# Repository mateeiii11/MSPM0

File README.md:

# MSPM0
MSMP0 designed in KiCad

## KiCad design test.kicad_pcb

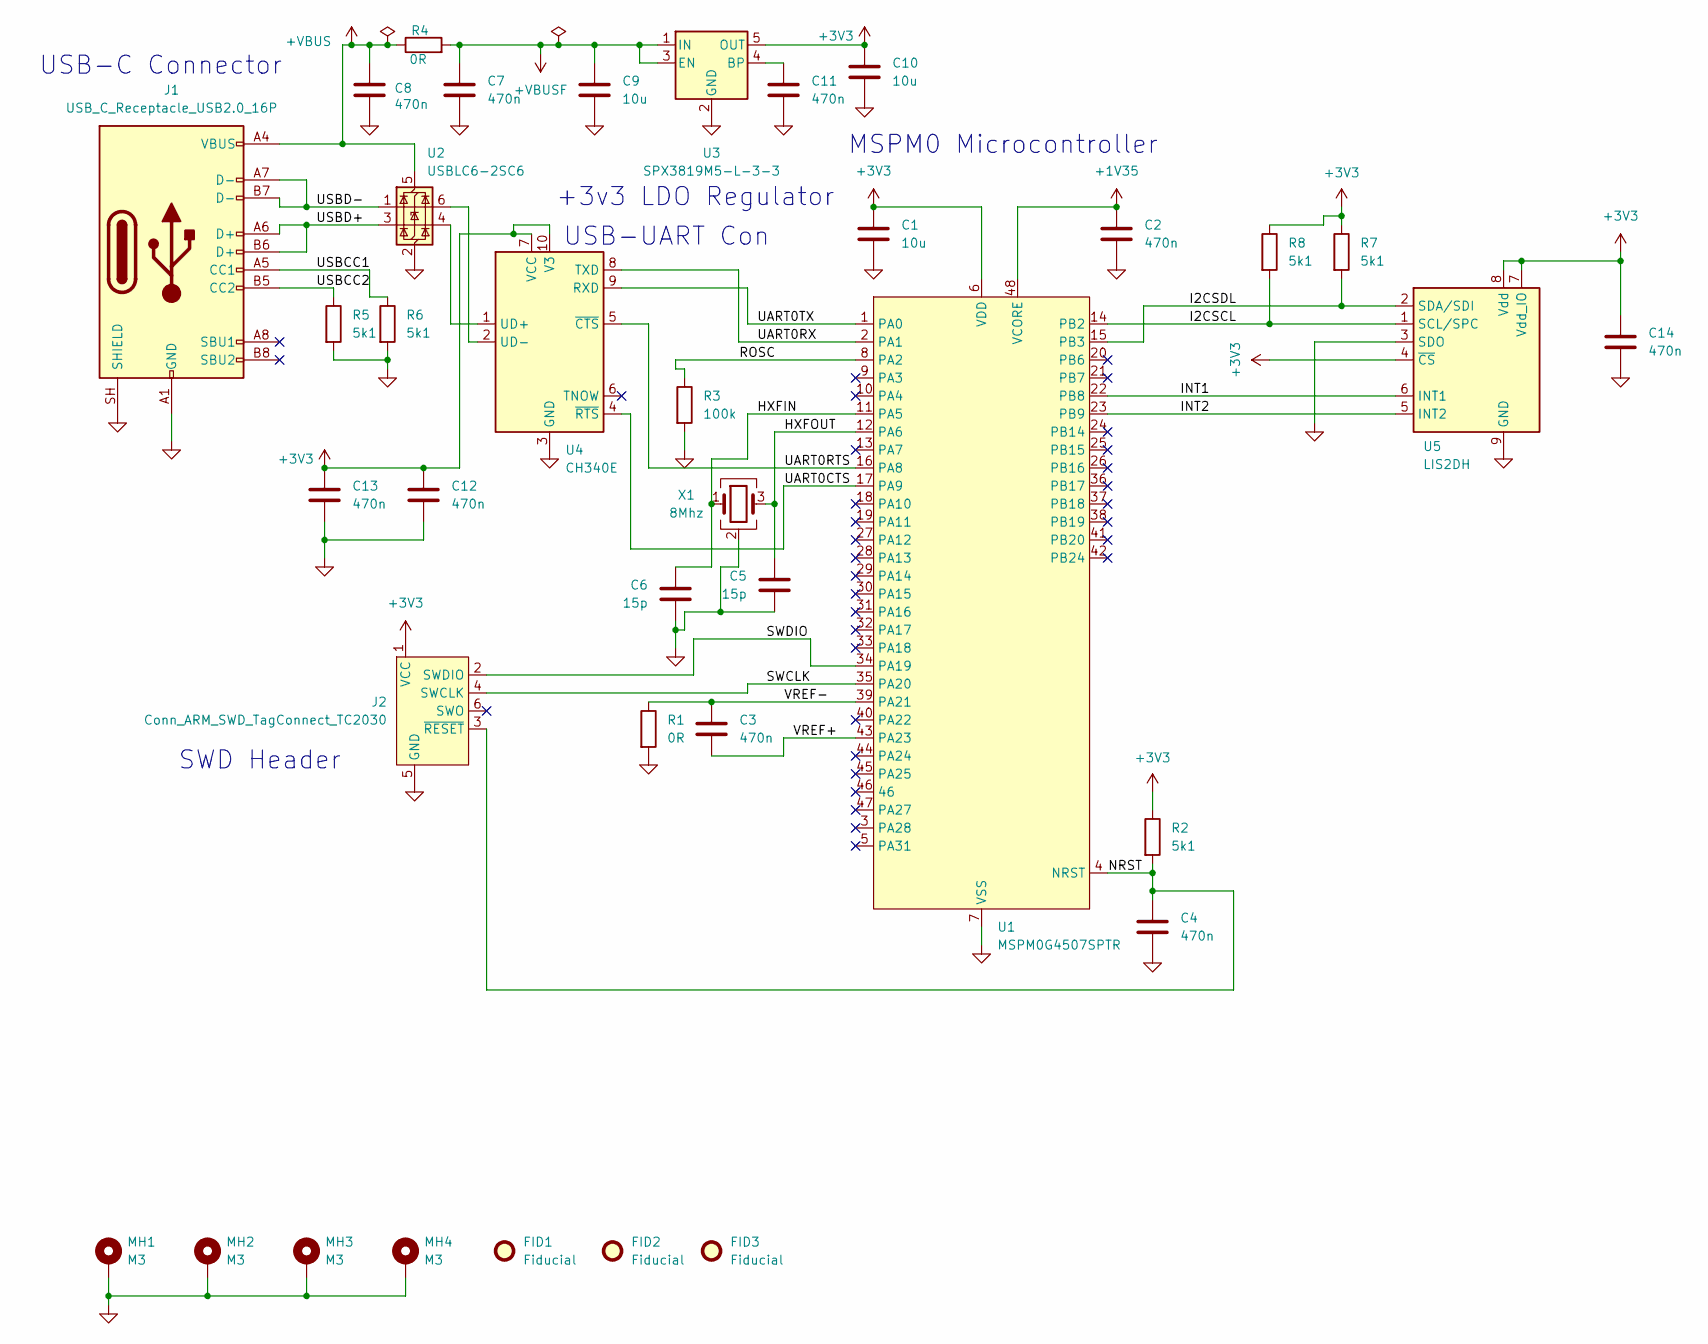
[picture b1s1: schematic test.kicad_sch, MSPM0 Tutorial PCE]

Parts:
C1, C9, C10: 10u; C_0805_2012Metric
C2, C3, C4, C7, C8, C11, C12, C13, C14: 470n; C_0805_2012Metric
C5, C6: 15p; C_0805_2012Metric
FID1, FID2, FID3: Fiducial; Fiducial_1mm_Mask2mm
J1: USB_C_Receptacle_USB2.0_16P; USB_C_Receptacle_GCT_USB4105-xx-A_16P_TopMnt_Horizontal
J2: Conn_ARM_SWD_TagConnect_TC2030; Tag-Connect_TC2030-IDC-FP_2x03_P1.27mm_Vertical
MH1, MH2, MH3, MH4: M3; MountingHole_3mm_Pad_Via
R1, R4: 0R; R_0603_1608Metric
R2, R5, R6, R7, R8: 5k1; R_0603_1608Metric
R3: 100k; R_0603_1608Metric
U1: MSPM0G4507SPTR; LQFP-48_7x7mm_P0.5mm; Manufacturer Part Number MSPM0G4507SPTR; LCSC C22362630
U2: USBLC6-2SC6; SOT-23-6
U3: SPX3819M5-L-3-3; SOT-23-5
U4: CH340E; MSOP-10_3x3mm_P0.5mm
U5: LIS2DH; LGA-14_2x2mm_P0.35mm_LayoutBorder3x4y
X1: 8Mhz; Crystal_SMD_3225-4Pin_3.2x2.5mm

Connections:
+1V35: C2.1, U1.48 (VCORE)
+3V3: C1.1, C10.1, C12.1, C13.1, C14.1, J2.1 (VCC), R2.1, R7.1, R8.1, U1.6 (VDD), U3.5 (OUT), U4.7 (VCC), U4.10 (V3), U5.4 (~CS), U5.7 (Vdd_IO), U5.8 (Vdd)
+VBUS: C8.1, J1.A4 (VBUS), J1.A9 (VBUS), J1.B4 (VBUS), J1.B9 (VBUS), R4.1, U2.5 (VBUS)
+VBUSF: C7.1, C9.1, R4.2, U3.1 (IN), U3.3 (EN)
/HXFIN: C6.1, U1.11 (PA5), X1.1
/HXFOUT: C5.1, U1.12 (PA6), X1.3
/I2CSCL: R8.2, U1.14 (PB2), U5.1 (SCL/SPC)
/I2CSDL: R7.2, U1.15 (PB3), U5.2 (SDA/SDI)
/INT1: U1.22 (PB8), U5.6 (INT1)
/INT2: U1.23 (PB9), U5.5 (INT2)
/NRST: C4.1, J2.3 (~RESET), R2.2, U1.4 (NRST)
/ROSC: R3.1, U1.8 (PA2)
/SWCLK: J2.4 (SWCLK), U1.35 (PA20)
/SWDIO: J2.2 (SWDIO), U1.34 (PA19)
/UART0CTS: U1.17 (PA9), U4.4 (~RTS)
/UART0RTS: U1.16 (PA8), U4.5 (~CTS)
/UART0RX: U1.2 (PA1), U4.8 (TXD)
/UART0TX: U1.1 (PA0), U4.9 (RXD)
/USBCC1: J1.A5 (CC1), R6.1
/USBCC2: J1.B5 (CC2), R5.1
/USBD+: J1.A6 (D+), J1.B6 (D+), U2.3 (I/O2)
/USBD-: J1.A7 (D-), J1.B7 (D-), U2.1 (I/O1)
/VREF+: C3.2, U1.43 (PA23)
/VREF-: C3.1, R1.1, U1.39 (PA21)
GND: C1.2, C2.2, C4.2, C5.2, C6.2, C7.2, C8.2, C9.2, C10.2, C11.2, C12.2, C13.2, C14.2, J1.A1 (GND), J1.A12 (GND), J1.B1 (GND), J1.B12 (GND), J1.SH (SHIELD), J2.5 (GND), MH1.1 (1_1), MH2.1 (1_1), MH3.1 (1_1), MH4.1 (1_1), R1.2, R3.2, R5.2, R6.2, U1.7 (VSS), U2.2 (GND), U3.2 (GND), U4.3 (GND), U5.3 (SDO), U5.9 (GND), X1.2 (G), X1.4 (G)
unnamed: C11.1, U3.4 (BP)
unnamed: U2.4 (I/O2), U4.1 (UD+)
unnamed: U2.6 (I/O1), U4.2 (UD-)
unnamed: U5.10 (GND), U5.11 (GND), U5.12 (GND), U5.13 (GND), U5.14 (GND)

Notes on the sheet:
SWD Header
USB-UART Con
USB-C Connector
MSPM0 Microcontroller
+3v3 LDO Regulator

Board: 2 copper layers, 37 parts (0 on the bottom side), 29 nets, no tracks yet.
